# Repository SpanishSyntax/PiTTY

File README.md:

# Qaz Personal Terminal

> A modern homage to the TRS-80 Model 100 — reimagined as a 33-key portable hacking terminal powered by the Raspberry Pi Compute Module 4.

---

## 🔧 What is this?

The **Qaz Personal Terminal** is a minimalist, portable hacking machine inspired by retro terminals like the Tandy Model 100. It's built around the **Raspberry Pi CM4**, exposing full GPIO access, USB, Wi-Fi, Bluetooth, and a compact 33-key mechanical keyboard layout based on the [Qaz](https://qmk.fm/keyboards/qaz/) form factor.

Perfect for:
- On-the-go terminal work
- Hardware hacking
- Tethered field ops
- Writing code in a ditch (probably)

---

## 📁 Repository Structure

```text
qaz-terminal/
├── 3d/                  # Fusion360 / STEP / STL files for enclosure
├── pcb/                 # KiCad schematics, layout, and fabrication files
├── renders/             # Product renders and screenshots
├── firmware/            # (optional) Firmware config for keyboard
├── docs/                # Assembly instructions, wiring diagrams, etc.
└── README.md
```

---

## 🧱 Features

- 🧠 **Compute Module 4 (CM4)** brain
- ⌨️ **33-key ortholinear keyboard** (Qaz-style)
- 🔌 **All IO pins exposed** (GPIO, UART, SPI, I2C)
- 📶 **Wi-Fi + Bluetooth onboard**
- 🧰 **USB ports** for debugging, flashing, or peripherals
- 📏 Compact, rugged enclosure with printed parts

---

## 📷 Renders

(See `/renders/` for all angles)

---

## ⚙️ 3D Enclosure

- Designed in **Fusion360**
- Exports available as **.STEP**, **.STL**, and **.F3D**
- Optimized for:
  - Printability (no supports required)
  - Snap-fit and screw-in parts
  - Ventilation and GPIO access

---

## 🔌 PCB Details

- Designed in **KiCad**
- Files include:
  - Schematic
  - Board layout
  - Gerbers & drill files
- Exposes:
  - 40-pin GPIO
  - 5V and 3.3V rails
  - USB
  - UART debug header

---

## 🖥️ Boot & Usage

1. Flash Raspberry Pi OS Lite (or custom image) to CM4
2. Connect via HDMI, SSH, or serial UART
3. Use any terminal, or customize for:
   - QMK firmware
   - Custom CLI tools
   - Field diagnostics

---

## 💡 Inspiration

The Qaz Personal Terminal is influenced by:
- TRS-80 Model 100
- Cyberdeck culture
- QMK & low-profile mechanical keyboards
- Minimalist UNIX workflows

---

## 📜 License

Open-source hardware & designs under **CERN-OHL-P v2**  
Documentation and code under **MIT License**  
*(See `/LICENSE.md` for full text)*

---

## 🛠️ Roadmap

- [ ] Optional battery support (LiPo + charging)
- [ ] Low-power display integration (OLED or epaper)
- [ ] Detachable antenna mod
- [ ] Bootloader flash jig
- [ ] Keyboard firmware configurator

---

## 🤝 Contribute / Fork

This project is a starting point — feel free to fork, remix, or help expand it.  
If you build one, [tag me](mailto:your@email.com) or drop a pull request!

---

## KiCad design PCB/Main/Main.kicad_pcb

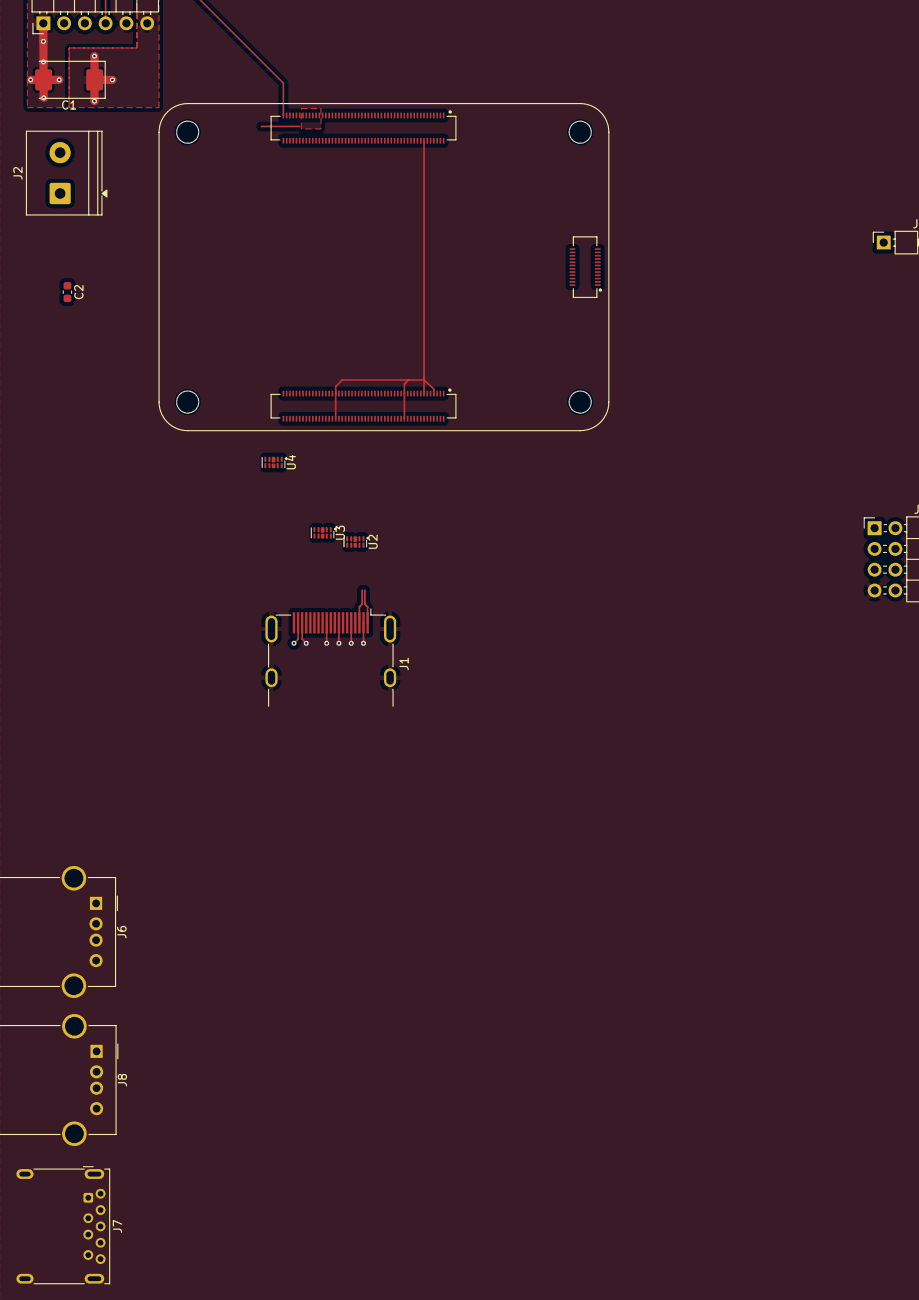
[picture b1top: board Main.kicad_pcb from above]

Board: 4 copper layers, 14 parts (0 on the bottom side), 38 nets.

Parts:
C1: 470µF; CP_EIA-7343-31_Kemet-D
C2: 100nF; C_0603_1608Metric
J1: HDMI_A_1.4; HDMI_A_Molex_208658-1001_Horizontal
J2: Conn_01x02_Pin; TerminalBlock_Phoenix_PT-1,5-2-5.0-H_1x02_P5.00mm_Horizontal
J3: Conn_01x01; PinHeader_1x01_P2.54mm_Horizontal
J4: Conn_02x04_Odd_Even; PinHeader_2x04_P2.54mm_Horizontal
J5: Conn_01x06; PinHeader_1x06_P2.54mm_Horizontal
J6, J8: USB_A; USB_A_Molex_67643_Horizontal
J7: USB3_A; USB3_A_Molex_48393-001
U1: ORANGE_PI_CM4; OCM4
U2, U3, U4: ESD224DQA; Diodes_UDFN-10_1x2.5mm_P0.5mm

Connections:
+5V: J1.18 (+5V), J2.1, J6.1 (VBUS), J7.1 (VBUS), J8.1 (VBUS), U1.JP1_77 (VBUS_JP1_77), U1.JP1_79 (VBUS_JP1_79), U1.JP1_81 (VBUS_JP1_81), U1.JP1_83 (VBUS_JP1_83), U1.JP1_85 (VBUS_JP1_85), U1.JP1_87 (VBUS_JP1_87)
/JP1/EN: J5.4, U1.JP1_99 (PMIC_PWRON)
/JP2/HDMI0_CEC: U1.JP2_51 (HDMI_CEC_PORT), U4.1
/JP2/HDMI0_CEC_IN: J1.13 (CEC), U4.10
/JP2/HDMI0_CLK_IN_N: J1.12 (CK-), U3.6
/JP2/HDMI0_CLK_IN_P: J1.10 (CK+), U3.7
/JP2/HDMI0_CLK_N: U1.JP2_90 (HDMI_TXCLKN_PORT), U3.5
/JP2/HDMI0_CLK_P: U1.JP2_88 (HDMI_TXCLKP_PORT), U3.4
/JP2/HDMI0_D0_IN_N: J1.9 (D0-), U3.9
/JP2/HDMI0_D0_IN_P: J1.7 (D0+), U3.10
/JP2/HDMI0_D0_N: U1.JP2_84 (HDMI_TX0N_PORT), U3.2
/JP2/HDMI0_D0_P: U1.JP2_82 (HDMI_TX0P_PORT), U3.1
/JP2/HDMI0_D1_IN_N: J1.6 (D1-), U2.6
/JP2/HDMI0_D1_IN_P: J1.4 (D1+), U2.7
/JP2/HDMI0_D1_N: U1.JP2_78 (HDMI_TX1N_PORT), U2.5
/JP2/HDMI0_D1_P: U1.JP2_76 (HDMI_TX1P_PORT), U2.4
/JP2/HDMI0_D2_IN_N: J1.3 (D2-), U2.9
/JP2/HDMI0_D2_IN_P: J1.1 (D2+), U2.10
/JP2/HDMI0_D2_N: U1.JP2_72 (HDMI_TX2N_PORT), U2.2
/JP2/HDMI0_D2_P: U1.JP2_70 (HDMI_TX2P_PORT), U2.1
/JP2/HDMI0_HPD: U1.JP2_53 (HDMI_TX_HPD_PORT), U4.5
/JP2/HDMI0_HPD_IN: J1.19 (HPD/HEAC-), U4.6
/JP2/HDMI0_SCL: U1.JP2_100 (HDMI_TXDDC_SCL_PORT), U4.2
/JP2/HDMI0_SCL_IN: J1.15 (SCL), U4.9
/JP2/HDMI0_SDA: U1.JP2_99 (HDMI_TXDDC_SDA_PORT), U4.4
/JP2/HDMI0_SDA_IN: J1.16 (SDA), U4.7
/Power/POWER_5V: C1.1, J5.6
/Power/POWER_GND: C1.2, J2.2, J5.1, J5.5
GND: J1.2 (D2S), J1.5 (D1S), J1.8 (D0S), J1.11 (CKS), J1.17 (GND), J1.SH, J4.7, J6.4 (GND), J6.5 (Shield), J7.4 (GND), J7.7 (DRAIN), J7.10 (SHIELD), J8.4 (GND), J8.5 (Shield), U1.JP1_1 (GND_JP1_1), U1.JP1_2 (GND_JP1_2), U1.JP1_7 (GND_JP1_7), U1.JP1_8 (GND_JP1_8), U1.JP1_13 (GND_JP1_13), U1.JP1_14 (GND_JP1_14), U1.JP1_22 (GND_JP1_22), U1.JP1_23 (GND_JP1_23), U1.JP1_32 (GND_JP1_32), U1.JP1_33 (GND_JP1_33), U1.JP1_42 (GND_JP1_42), U1.JP1_43 (GND_JP1_43), U1.JP1_52 (GND_JP1_52), U1.JP1_53 (GND_JP1_53), U1.JP1_59 (GND_JP1_59), U1.JP1_60 (GND_JP1_60), U1.JP1_65 (GND_JP1_65), U1.JP1_66 (GND_JP1_66), U1.JP1_71 (GND_JP1_71), U1.JP1_74 (GND_JP1_74), U1.JP1_98 (GND_JP1_98), U1.JP2_7 (GND_JP2_7), U1.JP2_8 (GND_JP2_8), U1.JP2_13 (GND_JP2_13), U1.JP2_14 (GND_JP2_14), U1.JP2_19 (GND_JP2_19), U1.JP2_20 (GND_JP2_20), U1.JP2_25 (GND_JP2_25), U1.JP2_26 (GND_JP2_26), U1.JP2_31 (GND_JP2_31), U1.JP2_32 (GND_JP2_32), U1.JP2_37 (GND_JP2_37), U1.JP2_38 (GND_JP2_38), U1.JP2_44 (GND_JP2_44), U1.JP2_50 (GND_JP2_50), U1.JP2_55 (GND_JP2_55), U1.JP2_56 (GND_JP2_56), U1.JP2_61 (GND_JP2_61), U1.JP2_62 (GND_JP2_62), U1.JP2_67 (GND_JP2_67), U1.JP2_68 (GND_JP2_68), U1.JP2_73 (GND_JP2_73), U1.JP2_74 (GND_JP2_74), U1.JP2_79 (GND_JP2_79), U1.JP2_80 (GND_JP2_80), U1.JP2_85 (GND_JP2_85), U1.JP2_86 (GND_JP2_86), U1.JP2_91 (GND_JP2_91), U1.JP2_92 (GND_JP2_92), U1.JP2_97 (GND_JP2_97), U1.JP2_98 (GND_JP2_98), U1.JP3_1 (GND_JP3_1), U1.JP3_2 (GND_JP3_2), U1.JP3_7 (GND_JP3_7), U1.JP3_13 (GND_JP3_13), U1.JP3_14 (GND_JP3_14), U1.JP3_17 (GND_JP3_17), U1.JP3_20 (GND_JP3_20), U1.JP3_23 (GND_JP3_23), U2.3 (VSS), U2.8 (VSS), U3.3 (VSS), U3.8 (VSS)
unnamed: J6.3 (D+), U1.JP3_5 (USB2_HOST3_DP)
unnamed: J6.2 (D-), U1.JP3_3 (USB2_HOST3_DM)
unnamed: J7.3 (D+), U1.JP3_21 (USB3_HOST1_DP)
unnamed: J7.2 (D-), U1.JP3_19 (USB3_HOST1_DM)
unnamed: J7.9 (SSTX+), U1.JP3_22 (USB3_HOST1_SSRXP)
unnamed: J7.8 (SSTX-), U1.JP3_24 (USB3_HOST1_SSRXN)
unnamed: J8.3 (D+), U1.JP3_11 (USB2_HOST2_DP)
unnamed: J8.2 (D-), U1.JP3_9 (USB2_HOST2_DM)
unnamed: U4.3 (VSS), U4.8 (VSS)

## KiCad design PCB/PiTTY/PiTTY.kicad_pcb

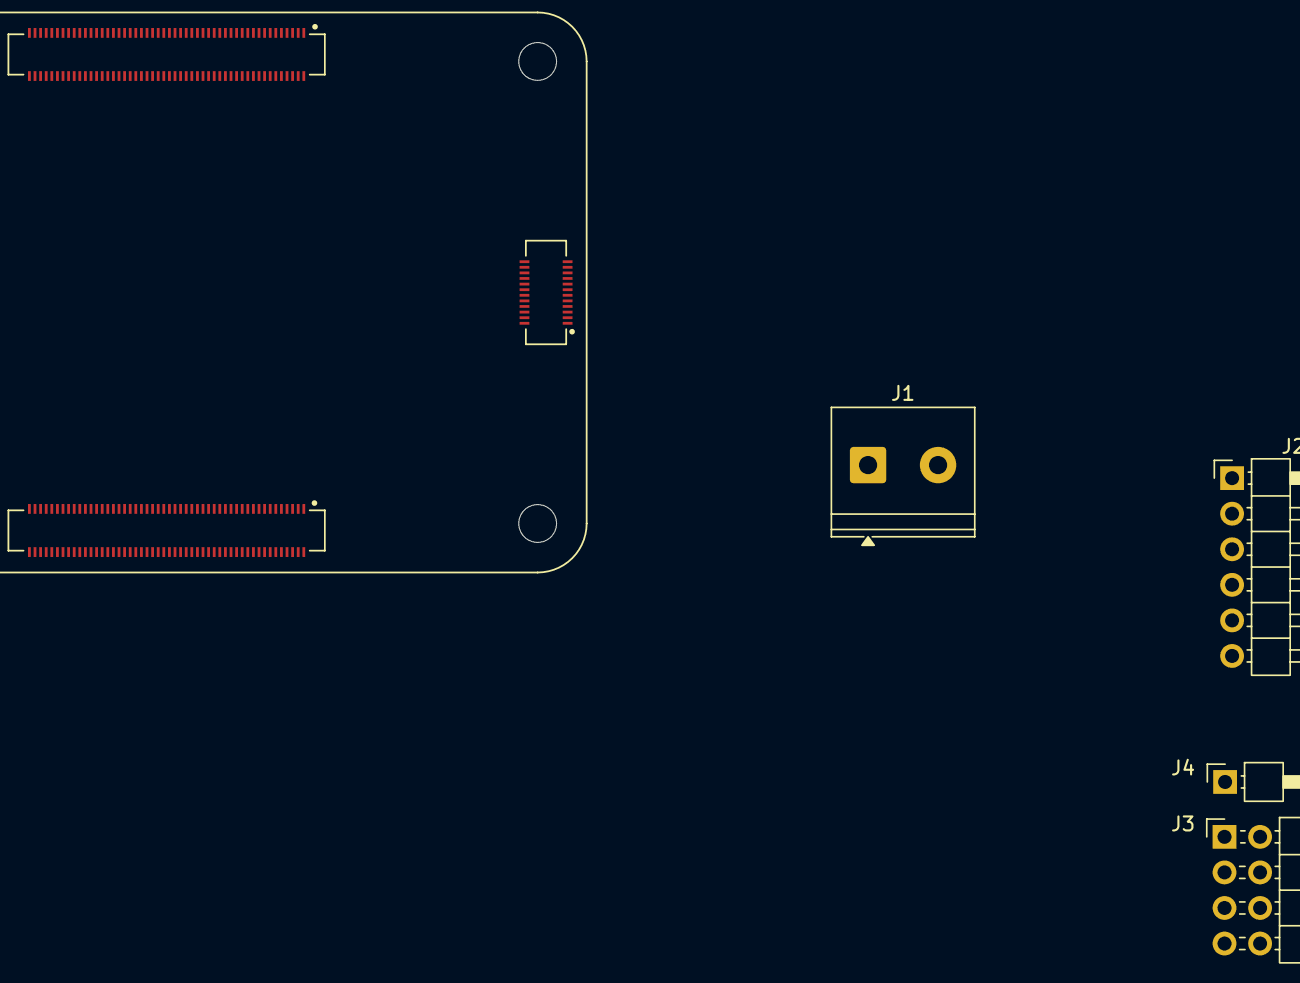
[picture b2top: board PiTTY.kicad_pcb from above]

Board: 2 copper layers, 5 parts (0 on the bottom side), 2 nets, no tracks yet.

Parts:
J1: Conn_01x02_Pin; TerminalBlock_Phoenix_PT-1,5-2-5.0-H_1x02_P5.00mm_Horizontal
J2: Conn_01x06; PinHeader_1x06_P2.54mm_Horizontal
J3: Conn_02x04_Odd_Even; PinHeader_2x04_P2.54mm_Horizontal
J4: Conn_01x01; PinHeader_1x01_P2.54mm_Horizontal
U1: ORANGE_PI_CM4; MODULE_ORANGE_PI_CM4

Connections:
+3.3V: J3.3, U1.JP1_84 (VCC_3V3_JP1_84)
GND: J1.2, J2.1, J2.5, J3.7

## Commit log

2026-02-12 Readme, gitignore and lfs
    Set up the repo for lfs support
2026-02-12 Base
    Messy files, but sends files to LFS. DONT TRUST
2026-02-23 readme y dots
2026-02-23 Assets
2026-02-23 PDFs
2026-02-23 OCM4 symbols and footprints
2026-02-23 ignore
2026-02-23 base
2026-02-23 power
2026-02-23 project
2026-02-23 asset libs
2026-02-23 renaming y basico sin pcb
2026-02-23 rename y conectores
    tambien se añaden pours
2026-02-27 pcb continued
2026-02-28 ampripper4000 symbol
2026-02-28 power with ampripper
2026-03-14 term draft
2026-03-14 simplify
2026-03-14 pitty
